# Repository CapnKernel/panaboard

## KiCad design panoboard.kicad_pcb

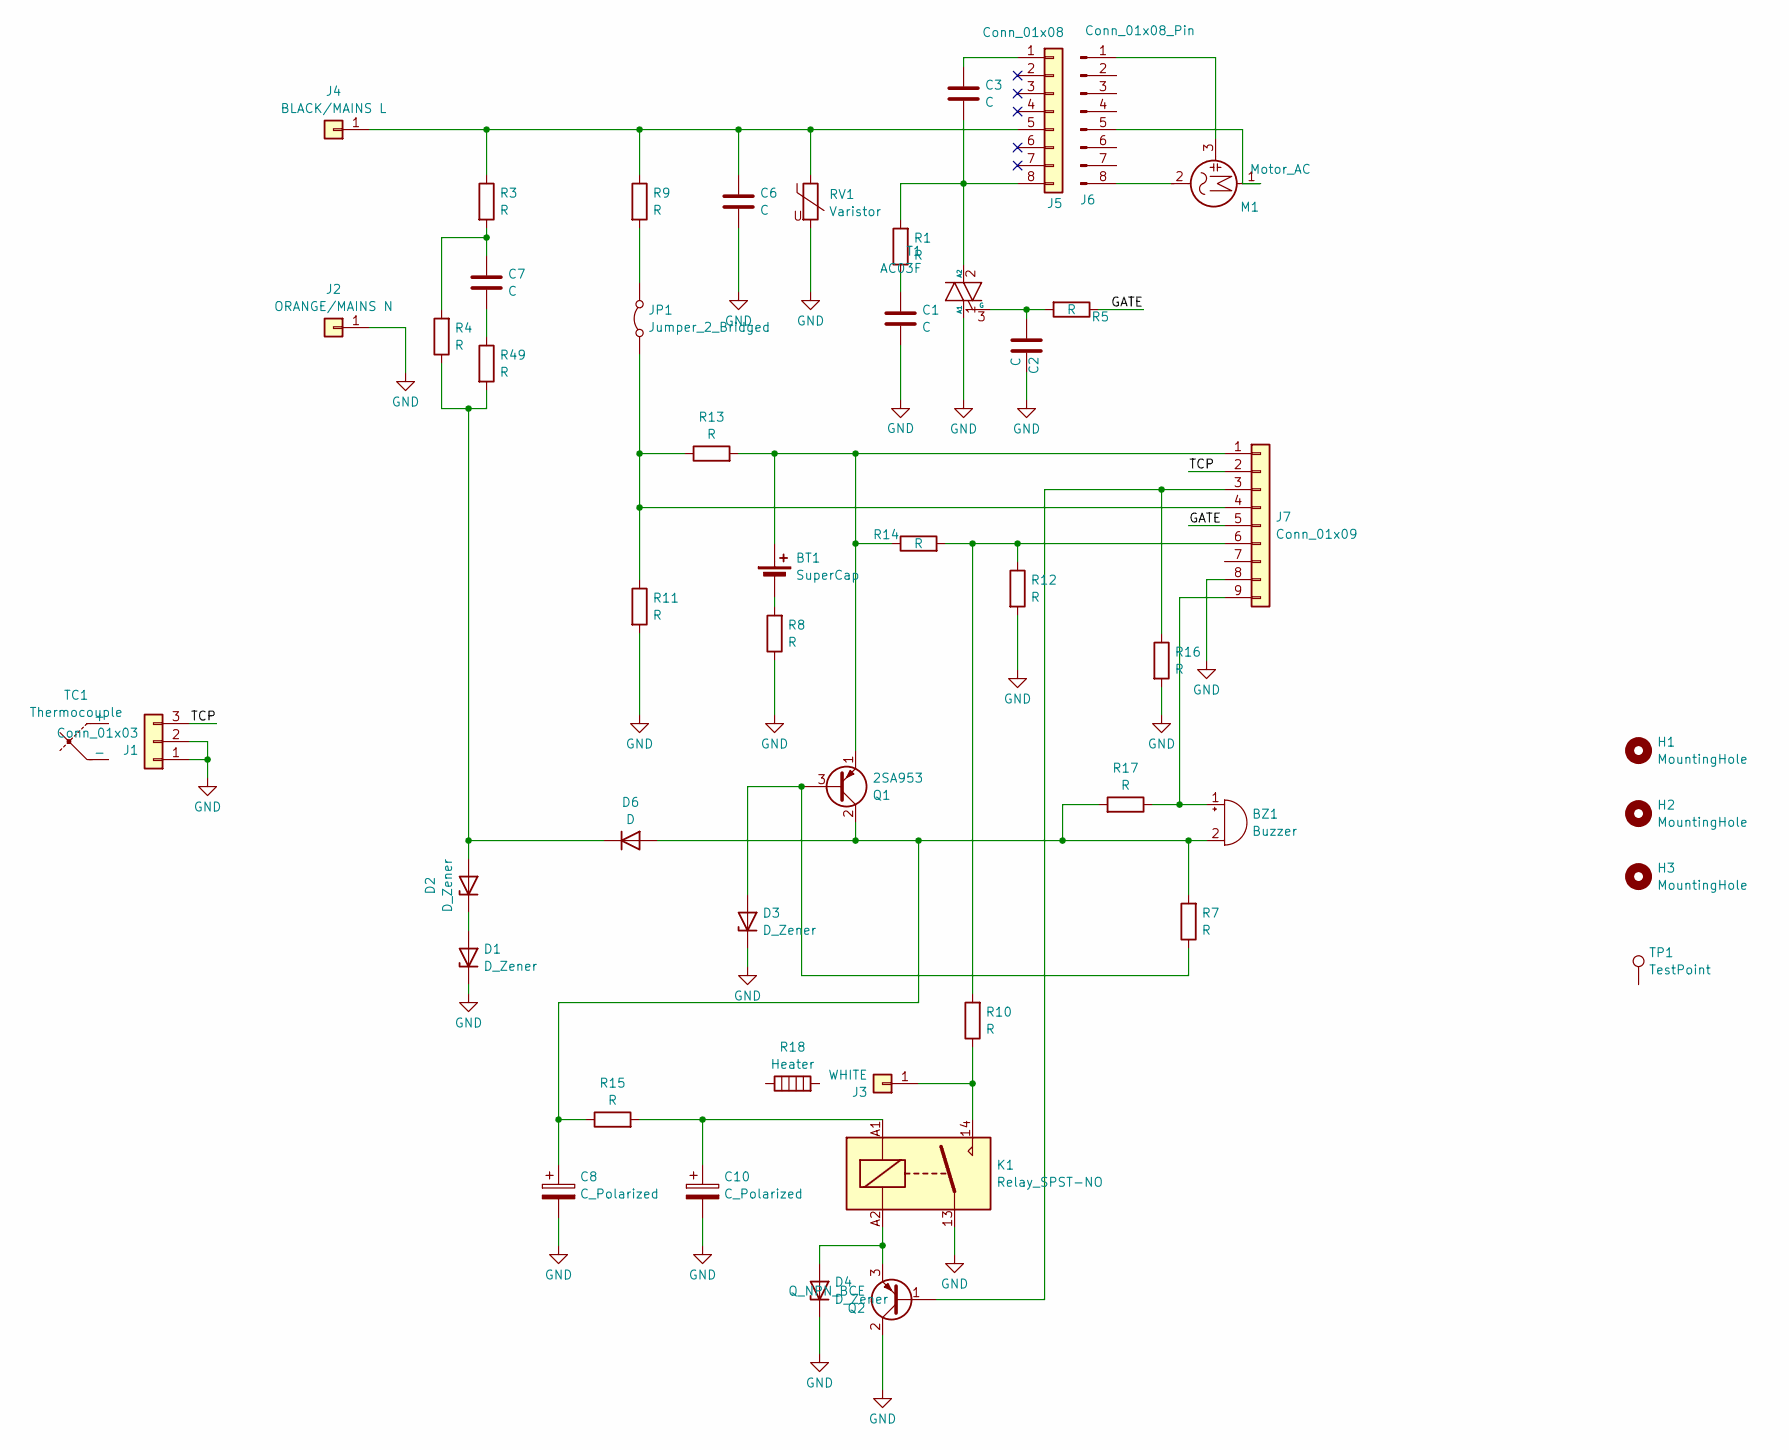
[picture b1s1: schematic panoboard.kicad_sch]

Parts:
BT1: SuperCap; DX_5R5VxxxxU_D11.5mm_P5.00mm
BZ1: Buzzer; MagneticBuzzer_CUI_CST-931RP-A
C1, C6: C; C_Rect_L7.0mm_W6.0mm_P5.00mm
C2: C; C_0805_2012Metric
C3: C; C_Rect_L41.5mm_W20.0mm_P37.50mm_MKS4
C7: C; C_Rect_L10.3mm_W5.7mm_P7.50mm_MKS4
C8: C_Polarized; C_Radial_D10.0mm_H12.5mm_P5.00mm
C10: C_Polarized; C_Radial_D5.0mm_H11.0mm_P2.00mm
D1, D2, D4: D_Zener; D_DO-41_SOD81_P10.16mm_Horizontal
D3: D_Zener; D_T-1_P5.08mm_Horizontal
D6: D; D_DO-41_SOD81_P10.16mm_Horizontal
H1, H2, H3: MountingHole; MountingHole_3.7mm
J1: Conn_01x03; PinHeader_1x03_P2.54mm_Vertical
J2: ORANGE/MAINS N; SolderWire-2sqmm_1x01_D2mm_OD3.9mm
J3: WHITE; SolderWire-2sqmm_1x01_D2mm_OD3.9mm
J4: BLACK/MAINS L; SolderWire-2sqmm_1x01_D2mm_OD3.9mm
J5: Conn_01x08; PinHeader_1x08_P2.54mm_Vertical
J6: Conn_01x08_Pin
J7: Conn_01x09; JST_ZE_B09B-ZESK-D_1x09_P1.50mm_Vertical
JP1: Jumper_2_Bridged; R_0805_2012Metric
K1: Relay_SPST-NO; Relay_SPST_Omron_G5PZ
M1: Motor_AC
Q1: 2SA953; TO-92_Inline
Q2: Q_NPN_BCE; SOT-23_Handsoldering
R1, R4, R9, R10, R15: R; R_Axial_DIN0207_L6.3mm_D2.5mm_P10.16mm_Horizontal
R3, R49: R; R_Axial_DIN0411_L9.9mm_D3.6mm_P12.70mm_Horizontal
R5, R7, R11, R12, R14, R16, R17: R; R_1206_3216Metric
R8, R13: R; R_Axial_DIN0204_L3.6mm_D1.6mm_P5.08mm_Horizontal
R18: Heater
RV1: Varistor; RV_Disc_D9mm_W5.2mm_P5mm
T1: AC03F; TO-202AA
TC1: Thermocouple
TP1: TestPoint

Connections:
/GATE: J7.5, R5.1
/TCP: J1.3, J7.2
GND: C1.2, C2.2, C6.1, C8.2, C10.2, D1.1 (K), D3.1 (K), D4.1 (K), J1.1, J1.2, J2.1, J7.8, K1.13, Q2.2 (C), R8.1, R11.2, R12.2, R16.2, RV1.2, T1.1 (A1)
unnamed: BT1.1 (+), J7.1, Q1.1 (E), R13.2, R14.1
unnamed: BT1.2 (-), R8.2
unnamed: BZ1.1 (+), J7.9, R17.1
unnamed: BZ1.2 (-), C8.1, D6.2 (A), Q1.2 (C), R7.2, R15.1, R17.2
unnamed: C1.1, R1.1
unnamed: C7.1, R49.1
unnamed: C7.2, R3.2, R4.2
unnamed: C10.1, K1.A1, R15.2
unnamed: D1.2 (A), D2.1 (K)
unnamed: D2.2 (A), D6.1 (K), R4.1, R49.2
unnamed: D3.2 (A), Q1.3 (B), R7.1
unnamed: D4.2 (A), K1.A2, Q2.3 (E)
unnamed: J3.1, K1.14, R10.1
unnamed: C6.2, J4.1, J5.5, R3.1, R9.1, RV1.1
unnamed: C3.1, J5.1
unnamed: C3.2, J5.8, R1.2, T1.2 (A2)
unnamed: J6.1, M1.3
unnamed: J6.5, M1.1
unnamed: J6.8, M1.2
unnamed: J7.3, Q2.1 (B), R16.1
unnamed: J7.4, JP1.1 (A), R11.1, R13.1
unnamed: J7.6, R10.2, R12.1, R14.2
unnamed: JP1.2 (B), R9.2
unnamed: C2.1, R5.2, T1.3 (G)

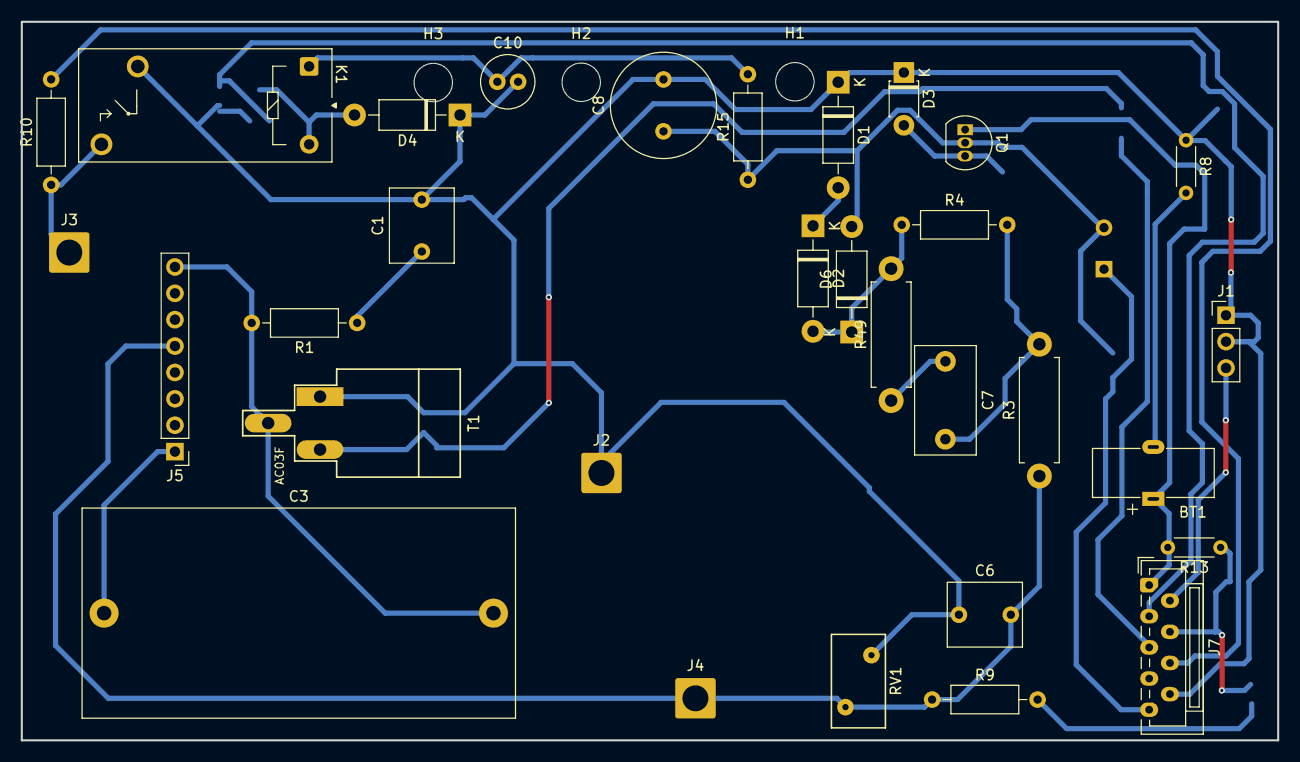
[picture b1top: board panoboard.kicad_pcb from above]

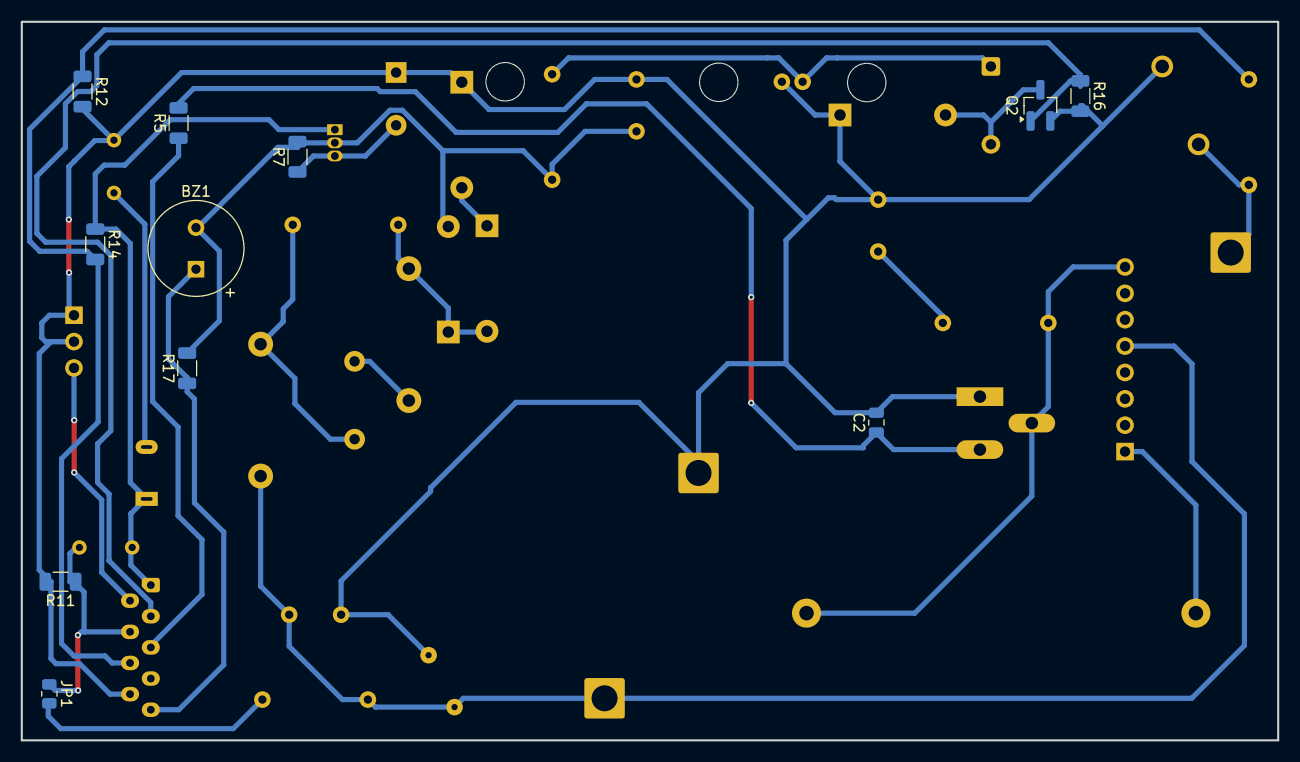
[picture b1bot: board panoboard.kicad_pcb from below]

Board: 2 copper layers, 121.0 x 69.2 mm, 45 parts (11 on the bottom side), 24 nets.
